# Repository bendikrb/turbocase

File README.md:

# Turbocase

Making a nice case for a PCB project is not terribly hard, but it is annoyingly time consuming if you just want a
simple functional case. This most of the time for a case design for me is spend on figuring out how to align the
mounting holes in the PCB with the 3D print and ensure the cutouts for the connectors are correct.

This project provides a ~~hacky~~ neat way to generate an OpenSCAD project based on the data in a KiCAD PCB file.

To define the shape of the case create a drawing of inside edge of the case on one of the user layers. This follows
the same semantics as the PCB fabrication outline on the Edge.Cuts layer. By default turbocase reads the outline from
the User.6 layer.

Turbocase will automatically extract information about MountingHole footprints and place plastic posts underneath the
PCB to fit threaded metal inserts after 3D printing. It currently is hardcoded to the bag of M3 inserts I have.

For connectors KiCAD needs to learn about the third dimension. For this purpose I have added a "Height" property to
the connects I want to be processed by turbocase that defines the height from the top of the PCB to the top of the
connector so an appropiate cutout can be made in the case. The rest of the shape of the connector is defined by the
bounding box of the F.Fab layer of the connector.

An example of a KiCAD PCB with a case outline on `User.6`:

The generated case from this file:

## Features in summary

* Generate a case from the shape defined on the `User.6` layer including holes for the bottom of the case.
* Generate a lid that fits on the case automatically. Holes defined in the `User.7` layer will be cut out of the lid.
* Generate mounting posts in the case that line up with the MountingHole footprints on the PCB
* Add bounding boxes for any footprint on the PCB that has a `Height` property defined (shown in red above).
* Automatically cut out the bounding boxes for those footprints from the case when clipping the walls.
* There is a library of extra footprints that instruct TurboCase to add extra features to the case like shaped screw
  holes and mounting posts for the lid.

## Installation

```shell-session
$ pip install turbocase
```

## Usage

1. Create a case outline in the `User.6` layer using the line drawing tools.
2. Add the `Height` property to the connector footprints that need to be in the case export
3. Ensure the screw holes for the PCB are MountingHole footprints
4. Run the turbocase tool to make an OpenSCAD file:

```shell-session
$ turbocase project/project.kicad_pcb case.scad
```

## Footprints

TurboCase can automatically add prefab structures to the generated case by using the included KiCad library.
The TurboCase.pretty folder in this repository is the footprint library that defines custom objects to add to the
design of your case. The tool will detect any footprints that start with `TurboCase:` and append the correct module
from `parts.py` into the final OpenSCAD file.

## Command line options

```
usage: turbocase [-h] [--layer LAYER] [--lid-layer LID_LAYER] [--bottom BOTTOM] [--wall WALL] [--standoff STANDOFF] [--show-pcb SHOW_PCB] [--lid {cap,inner-fit}] [--verbose] [--debug] pcb output

positional arguments:
  pcb                   Input kicad PCB file
  output                Generated openSCAD case template

options:
  -h, --help            show this help message and exit
  --layer LAYER         Layer with the case inner-outline [defaults to User.6]
  --lid-layer LID_LAYER
                        Layer with lid-specific holes [defaults to User.7]
  --bottom BOTTOM       Bottom thickness in mm [default 1.2]
  --wall WALL           Wall thickness in mm [default 1.2]
  --standoff STANDOFF   Height generated for the PCB mounts in mm[default 5]
  --show-pcb SHOW_PCB   Show the PCB placeholder by default [default false]
  --lid {cap,inner-fit}
                        Lid construction model
  --verbose, -v         Show log messages
  --debug               Display a lot of debugging info
```

## Contributing

The official repositories for this project
are [https://sr.ht/~martijnbraam/turbocase/](https://sr.ht/~martijnbraam/turbocase/)
and [https://codeberg.org/MartijnBraam/TurboCase](https://codeberg.org/MartijnBraam/TurboCase). Patches can be sent to
Codeberg as a pull request or to sr.ht using [git-send-email](https://git-send-email.io/):

```shell-session
$ git config sendemail.to "~martijnbraam/public-inbox@lists.sr.ht"
$ git send-email HEAD^
```

If you'd like to support development of this project and several others like this financially consider contributing to
my [Liberapay](https://liberapay.com/MartijnBraam) or [Patreon](https://www.patreon.com/martijnbraam).

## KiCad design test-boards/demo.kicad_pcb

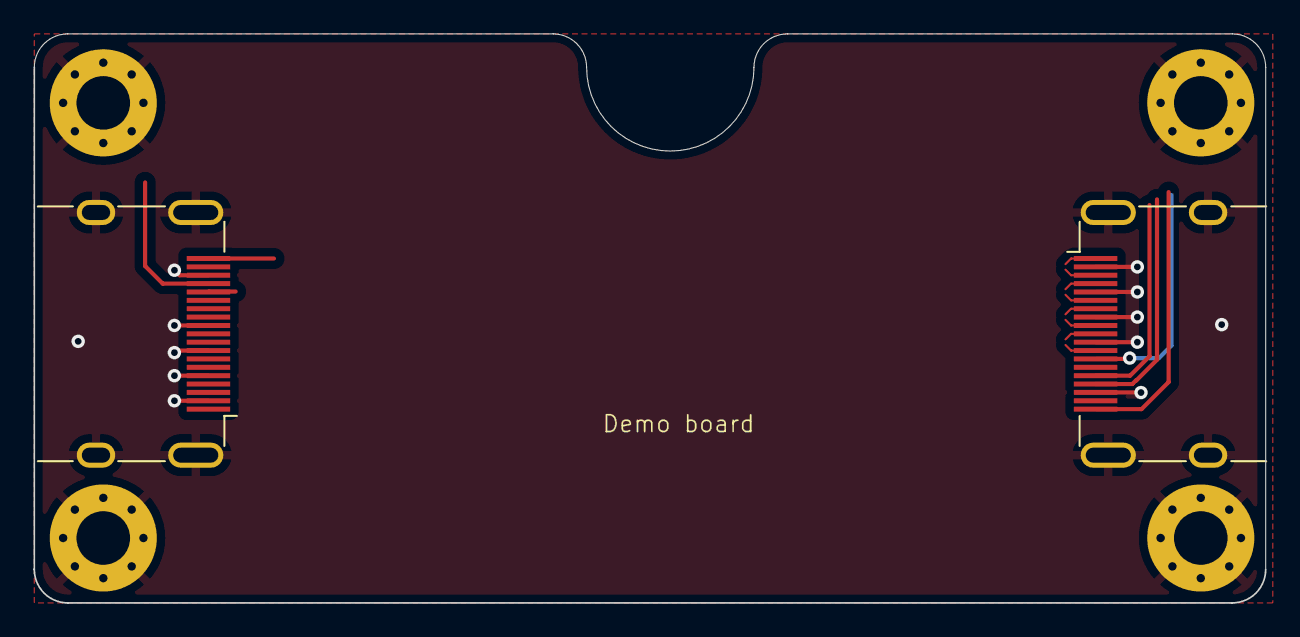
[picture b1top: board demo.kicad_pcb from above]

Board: 4 copper layers, 73.6 x 34.0 mm, 6 parts (0 on the bottom side), 10 nets.

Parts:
H3, H4, H5, H6: MountingHole_3.2mm_M3_Pad_Via
J1: Transmitter; HDMI_A_Molex_208658-1001_Horizontal
J2: Camera; HDMI_A_Molex_208658-1001_Horizontal

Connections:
/CK+: J1.10 (CK+), J2.10 (CK+)
/CK-: J1.12 (CK-), J2.12 (CK-)
/D0+: J1.7 (D0+), J2.7 (D0+)
/D0-: J1.9 (D0-), J2.9 (D0-)
/D1+: J1.4 (D1+), J2.4 (D1+)
/D1-: J1.6 (D1-), J2.6 (D1-)
/D2+: J1.1 (D2+), J2.1 (D2+)
/D2-: J1.3 (D2-), J2.3 (D2-)
GND: H3.1, H4.1, H5.1, H6.1, J1.2 (D2S), J1.5 (D1S), J1.8 (D0S), J1.11 (CKS), J1.17 (GND), J1.SH, J2.2 (D2S), J2.5 (D1S), J2.8 (D0S), J2.11 (CKS), J2.17 (GND), J2.SH
unnamed: J1.14 (UTILITY), J2.14 (UTILITY)

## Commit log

2024-05-15 Add LICENSE
2024-05-15 Add documentation images
2024-05-15 Update usage documentation
2024-05-15 Make the wall and bottom thickness configurable
2024-05-15 Implement gr_arc in the case outline
2024-05-15 Implement gr_rect and gr_poly as outlines
2024-05-15 Bump version to 1.2
2024-05-17 Fix mounting point generation and add prefabs
2024-05-17 Add the KiCad footprint library
2024-05-17 Bump version to 1.3
2024-05-17 Add footprint info to the README
2024-05-17 Add support for cutting holes
2024-05-17 Unmirror the generated cases
    The Y axis in the KiCad coordinate system is inverted compared to the OpenSCAD one...
2024-05-17 The battery should actually fit in the generated case
2024-05-17 Correctly calculate the height needed to fit in custom parts
2024-05-17 Generate footprints from classes
2024-05-17 Don't crash on connectors without F.Fab outline
2024-05-17 Fix formatting of error message
2024-05-26 Generate better KiCad footprints
2024-05-26 Add Type-C cutout to library
2024-05-26 Bump version to 1.4
2024-05-27 Make the standoff height fully parametric
2024-05-27 Add the parts subpackage to the pypi package and bump to 1.4.1
2024-05-27 Don't assume that all footprints containing the word "MountingHole" are mounting holes.
2024-05-27 Bump version to 1.4.2
2024-05-29 Fix connector shape rotation
2024-05-29 Insert board into the case as a module
2024-05-29 Add mounting holes to pcb shape holes
2024-05-29 Bump version to 1.5.0
2024-05-29 Don't show the rendered PCB by default
2024-05-29 Make the show_pcb variable a cmdline argument
2024-05-30 Implement very basic lid generation
2024-05-30 Add support for inside-contrained shapes and case corners
2024-05-30 Add case lid posts
2024-05-30 Support holes in the lid using the User.7 layer
2024-05-31 Improve cutouts and add a PCB snap-in mount feature
2024-05-31 Don't use $fn for circle resolution, use global $fs and $fa
2024-06-01 Add threaded inserts to the PCB mounts and the case corners
2024-06-01 Add two more mounting hole sizes from kicad
2024-06-01 Add slope for easier insert installation
2024-06-01 Improve initial headroom calculation with inserted cutouts
2024-06-01 Add cutout for standard 2.54mm pinheaders
2024-06-01 Add clips to snap the lid closed
2024-06-02 Improve the lid clip shape
2024-06-03 Add verbose and debug info with cmdline flags
2024-06-03 Fix height debug message
2024-06-03 Optimize printing time for the 18650 battery footprints and add text support
2024-06-03 Add missing description for the KeyHole parts
2024-06-03 Bump version to 1.6
2024-06-03 Render new screenshots for the readme
2024-06-03 Update command line options in the readme
2024-06-03 Bump version to 1.6.1
2024-06-06 Add Neutrik D-style chassis holes
2024-06-06 Add hole for the CUI SJ1-353x 3.5mmm jack
2024-06-06 Add newline to the README to appease the codeberg renderer
2024-06-07 Update readme with more information
2024-06-07 Add syntax highlighting for the git-send-email commands
2024-06-07 Support exporting SVG files for laser cutters
2024-06-11 Don't crash on holes without a reference set
    KiCad 7 doesn't add an empty reference for footprints so don't crash if it's not set.
2024-06-17 Use proper calculation for generating the arc points in the PCB and case path
2024-06-19 Escape insert names to fix OpenSCAD syntax error
    Avoid generating variables like `insert_M2.5_depth`
2024-06-19 Support circular PCBs and case outlines
2024-06-20 Don't crash on empty shapes
2024-06-20 Bump version to 1.7.0
2024-06-20 Fix crash on circular hole
2024-06-20 Fix crash on polygon edge.cuts
2024-06-20 Bump version to 1.7.1
2024-07-05 Use fuzzy matching for outline building
    Sometimes the coordinates of "connected" drawing segments is off by a floating point error. Use fuzzy matching to complete the outline anyway.
2024-07-05 Generate a placeholder case outline when none is defined on User.6
2024-07-22 Support adding OpenSCAD code to KiCad footprint properties to use them outside the TurboCase library.
2024-07-22 Add module docs to the part modules
    Used for generating the website.
2024-07-22 Bump version to 1.8.0
2024-07-22 Update screenshots for readme to show the new arc interpolation
